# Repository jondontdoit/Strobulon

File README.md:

# Strobulon! The LED Helmet

Code and project files for my wearable LED helmet

https://jhwarren.com/projects/Strobulon/

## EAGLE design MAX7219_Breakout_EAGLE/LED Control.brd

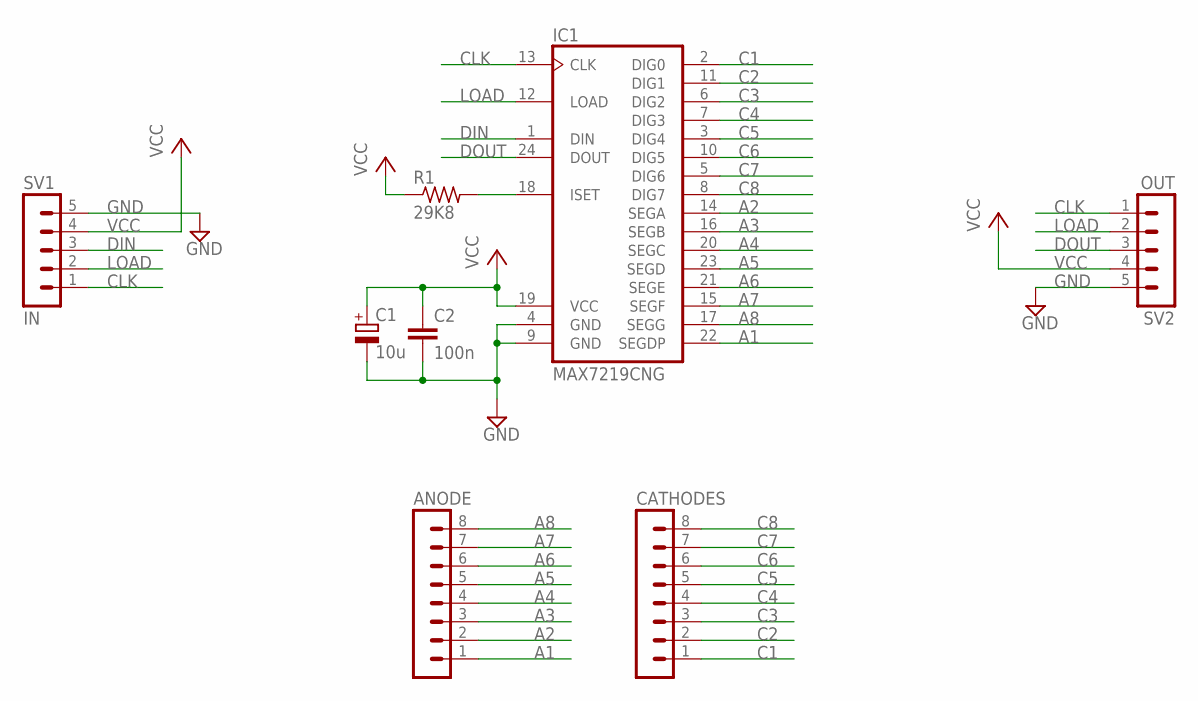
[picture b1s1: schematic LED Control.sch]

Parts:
ANODE: MA08-1
C1: 10u; E2-5
C2: 100n; C025-025X050
CATHODES: MA08-1
IC1: MAX7219CNG; DIL24-3
R1: 29K8; 0204/7
SV1: IN; MA05-1
SV2: OUT; MA05-1

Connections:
A1: ANODE.1, IC1.22 (SEGDP)
A2: ANODE.2, IC1.14 (SEGA)
A3: ANODE.3, IC1.16 (SEGB)
A4: ANODE.4, IC1.20 (SEGC)
A5: ANODE.5, IC1.23 (SEGD)
A6: ANODE.6, IC1.21 (SEGE)
A7: ANODE.7, IC1.15 (SEGF)
A8: ANODE.8, IC1.17 (SEGG)
C1: CATHODES.1, IC1.2 (DIG0)
C2: CATHODES.2, IC1.11 (DIG1)
C3: CATHODES.3, IC1.6 (DIG2)
C4: CATHODES.4, IC1.7 (DIG3)
C5: CATHODES.5, IC1.3 (DIG4)
C6: CATHODES.6, IC1.10 (DIG5)
C7: CATHODES.7, IC1.5 (DIG6)
C8: CATHODES.8, IC1.8 (DIG7)
CLK: IC1.13 (CLK), SV1.1, SV2.1
DIN: IC1.1 (DIN), SV1.3
DOUT: IC1.24 (DOUT), SV2.3
GND: C1.-, C2.2, IC1.4 (GND), IC1.9 (GND), SV1.5, SV2.5
LOAD: IC1.12 (LOAD), SV1.2, SV2.2
unnamed: IC1.18 (ISET), R1.2
VCC: C1.+, C2.1, IC1.19 (VCC), R1.1, SV1.4, SV2.4

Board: 2 copper layers, 8 parts (0 on the bottom side), 23 nets, no tracks yet.
